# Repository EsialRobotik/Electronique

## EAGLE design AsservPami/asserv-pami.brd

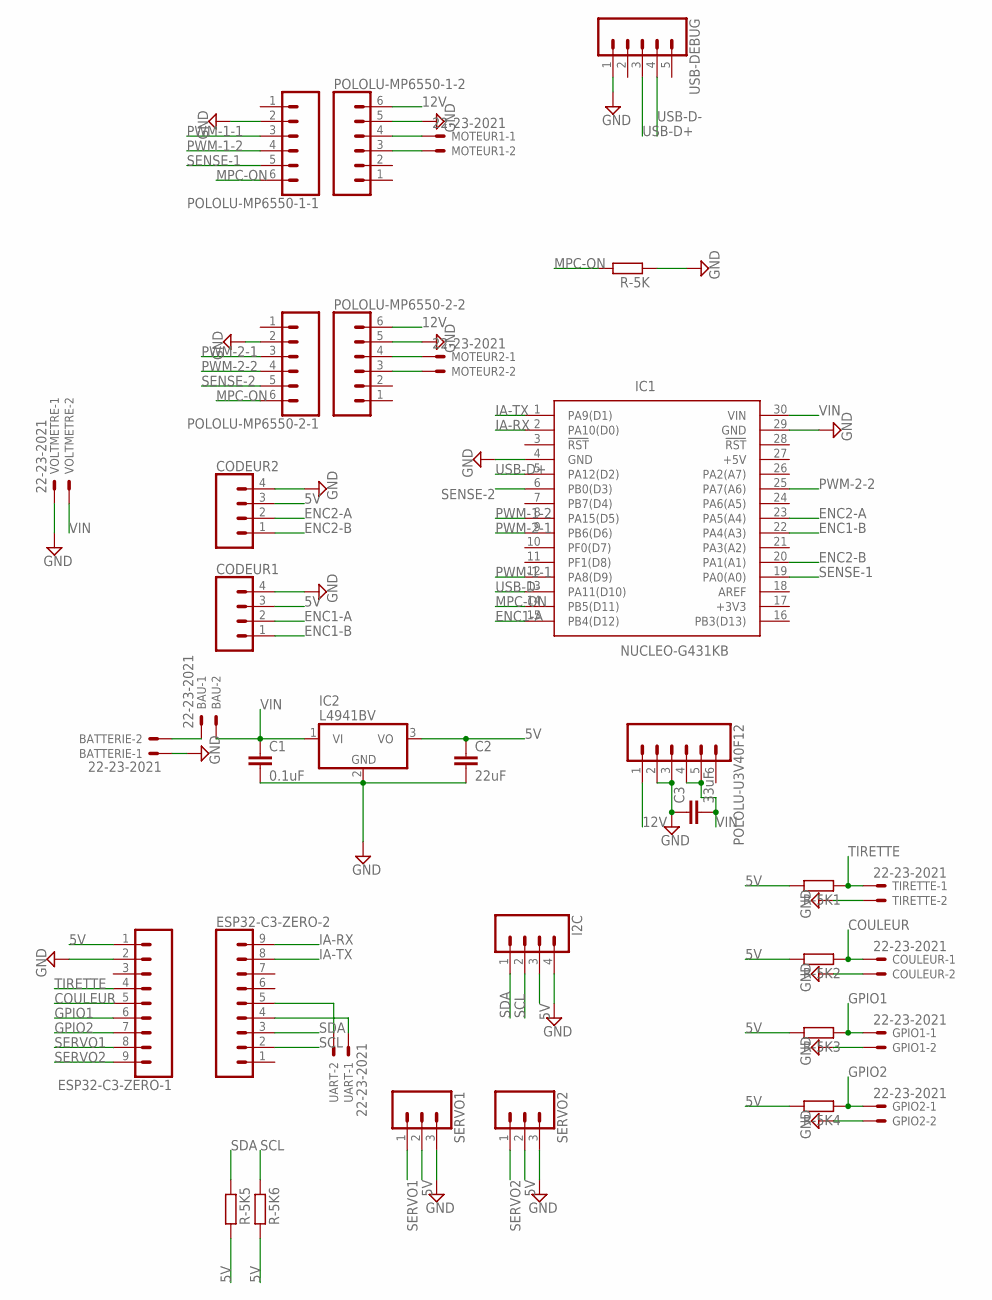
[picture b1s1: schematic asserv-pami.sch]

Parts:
BATTERIE: 22-23-2021
BAU: 22-23-2021
C1: 0.1uF; C5B2.5
C2: 22uF; C5B2.5
C3: 33uF; C5B2.5
CODEUR1, CODEUR2: CONN_04PTH; 1X04
COULEUR: 22-23-2021
ESP32-C3-ZERO-1, ESP32-C3-ZERO-2: CONN_09LONGPADS; 1X09_LONGPADS
GPIO1, GPIO2: 22-23-2021
I2C: CONN_04PTH; 1X04
IC1: NUCLEO-G431KB; DIPS1524W66P254L5029H1500Q30N
IC2: L4941BV; TO220V
MOTEUR1, MOTEUR2: 22-23-2021
POLOLU-MP6550-1-1, POLOLU-MP6550-1-2, POLOLU-MP6550-2-1, POLOLU-MP6550-2-2: CONN_06NO_SILK_FEMALE_PTH; 1X06_NO_SILK
POLOLU-U3V40F12: CONN_06NO_SILK_FEMALE_PTH; 1X06_NO_SILK
R-5K, R-5K1, R-5K2, R-5K3, R-5K4, R-5K5, R-5K6: R-EU_0204/7; 0204/7
SERVO1, SERVO2: CONN_03LONGPADS; 1X03_LONGPADS
TIRETTE: 22-23-2021
UART: 22-23-2021
USB-DEBUG: CONN_05NO_SILK; 1X05_NO_SILK
VOLTMETRE: 22-23-2021

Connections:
5V: C2.1, CODEUR1.3, CODEUR2.3, ESP32-C3-ZERO-1.1, I2C.3, IC2.3 (VO), R-5K1.2, R-5K2.2, R-5K3.2, R-5K4.2, R-5K5.2, R-5K6.2, SERVO1.2, SERVO2.2
12V: POLOLU-MP6550-1-2.6, POLOLU-MP6550-2-2.6, POLOLU-U3V40F12.1
COULEUR: COULEUR.1, ESP32-C3-ZERO-1.5, R-5K2.1
ENC1-A: CODEUR1.2, IC1.15 (PB4(D12))
ENC1-B: CODEUR1.1, IC1.22 (PA4(A3))
ENC2-A: CODEUR2.2, IC1.23 (PA5(A4))
ENC2-B: CODEUR2.1, IC1.20 (PA1(A1))
GND: BATTERIE.1, C1.2, C2.2, C3.1, CODEUR1.4, CODEUR2.4, COULEUR.2, ESP32-C3-ZERO-1.2, GPIO1.2, GPIO2.2, I2C.4, IC1.4 (GND), IC1.29 (GND), IC2.2 (GND), POLOLU-MP6550-1-1.2, POLOLU-MP6550-1-2.5, POLOLU-MP6550-2-1.2, POLOLU-MP6550-2-2.5, POLOLU-U3V40F12.2, POLOLU-U3V40F12.3, R-5K.1, SERVO1.3, SERVO2.3, TIRETTE.2, USB-DEBUG.1, VOLTMETRE.1
GPIO1: ESP32-C3-ZERO-1.6, GPIO1.1, R-5K3.1
GPIO2: ESP32-C3-ZERO-1.7, GPIO2.1, R-5K4.1
IA-RX: ESP32-C3-ZERO-2.9, IC1.2 (PA10(D0))
IA-TX: ESP32-C3-ZERO-2.8, IC1.1 (PA9(D1))
MPC-ON: IC1.14 (PB5(D11)), POLOLU-MP6550-1-1.6, POLOLU-MP6550-2-1.6, R-5K.2
unnamed: MOTEUR1.1, POLOLU-MP6550-1-2.4
unnamed: MOTEUR1.2, POLOLU-MP6550-1-2.3
unnamed: MOTEUR2.1, POLOLU-MP6550-2-2.4
unnamed: MOTEUR2.2, POLOLU-MP6550-2-2.3
unnamed: ESP32-C3-ZERO-2.4, UART.1
unnamed: ESP32-C3-ZERO-2.5, UART.2
unnamed: BATTERIE.2, BAU.1
PWM-1-1: IC1.12 (PA8(D9)), POLOLU-MP6550-1-1.3
PWM-1-2: IC1.8 (PA15(D5)), POLOLU-MP6550-1-1.4
PWM-2-1: IC1.9 (PB6(D6)), POLOLU-MP6550-2-1.3
PWM-2-2: IC1.25 (PA7(A6)), POLOLU-MP6550-2-1.4
SCL: ESP32-C3-ZERO-2.2, I2C.2, R-5K6.1
SDA: ESP32-C3-ZERO-2.3, I2C.1, R-5K5.1
SENSE-1: IC1.19 (PA0(A0)), POLOLU-MP6550-1-1.5
SENSE-2: IC1.6 (PB0(D3)), POLOLU-MP6550-2-1.5
SERVO1: ESP32-C3-ZERO-1.8, SERVO1.1
SERVO2: ESP32-C3-ZERO-1.9, SERVO2.1
TIRETTE: ESP32-C3-ZERO-1.4, R-5K1.1, TIRETTE.1
USB-D+: IC1.5 (PA12(D2)), USB-DEBUG.3
USB-D-: IC1.13 (PA11(D10)), USB-DEBUG.4
VIN: BAU.2, C1.1, C3.2, IC1.30 (VIN), IC2.1 (VI), POLOLU-U3V40F12.4, POLOLU-U3V40F12.5, VOLTMETRE.2

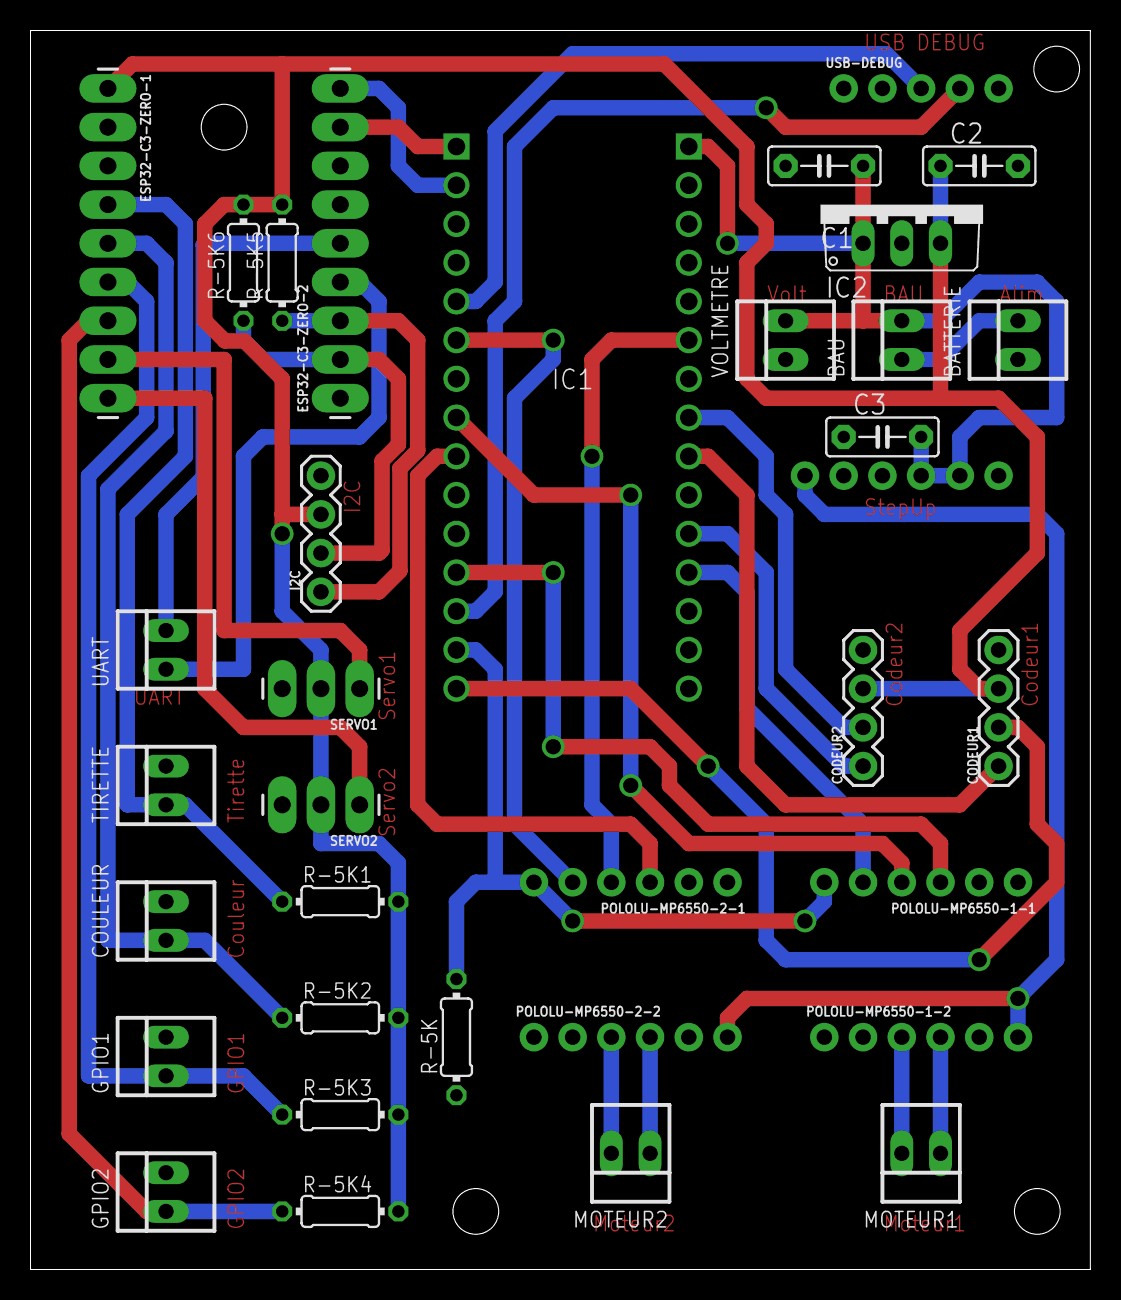
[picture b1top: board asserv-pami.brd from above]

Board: 2 copper layers, 69.5 x 81.3 mm, 35 parts (0 on the bottom side), 34 nets.

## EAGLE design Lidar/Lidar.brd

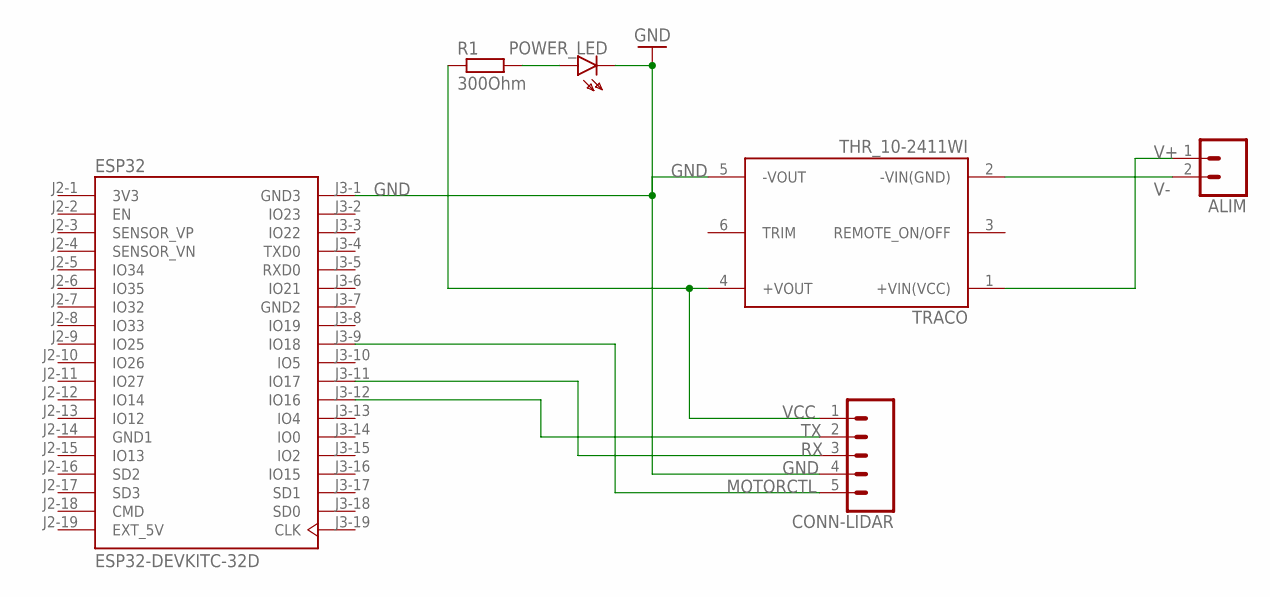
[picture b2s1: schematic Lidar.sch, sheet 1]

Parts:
ALIM: CONN_02POLAR; MOLEX-1X2
CONN-LIDAR: CONN_05PTH; 1X05
ESP32: ESP32-DEVKITC-32D; MODULE_ESP32-DEVKITC-32D
POWER_LED: HLMP6
R1: 300Ohm; 0411/15
TRACO: THR_10-2411WI; CONV_THR_10-2411WI

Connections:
3V3: ESP32.J2-1 (3V3)
GND: CONN-LIDAR.4, ESP32.J3-1 (GND3), POWER_LED.K, TRACO.5 (-VOUT)
GND1: ESP32.J2-14 (GND1)
GND2: ESP32.J3-7 (GND2)
MOTORCTL: CONN-LIDAR.5, ESP32.J3-9 (IO18)
unnamed: POWER_LED.A, R1.2
RX: CONN-LIDAR.3, ESP32.J3-11 (IO17)
TX: CONN-LIDAR.2, ESP32.J3-12 (IO16)
V+: ALIM.1, TRACO.1 (+VIN(VCC))
V-: ALIM.2, TRACO.2 (-VIN(GND))
VCC: CONN-LIDAR.1, ESP32.J2-19 (EXT_5V), R1.1, TRACO.4 (+VOUT)

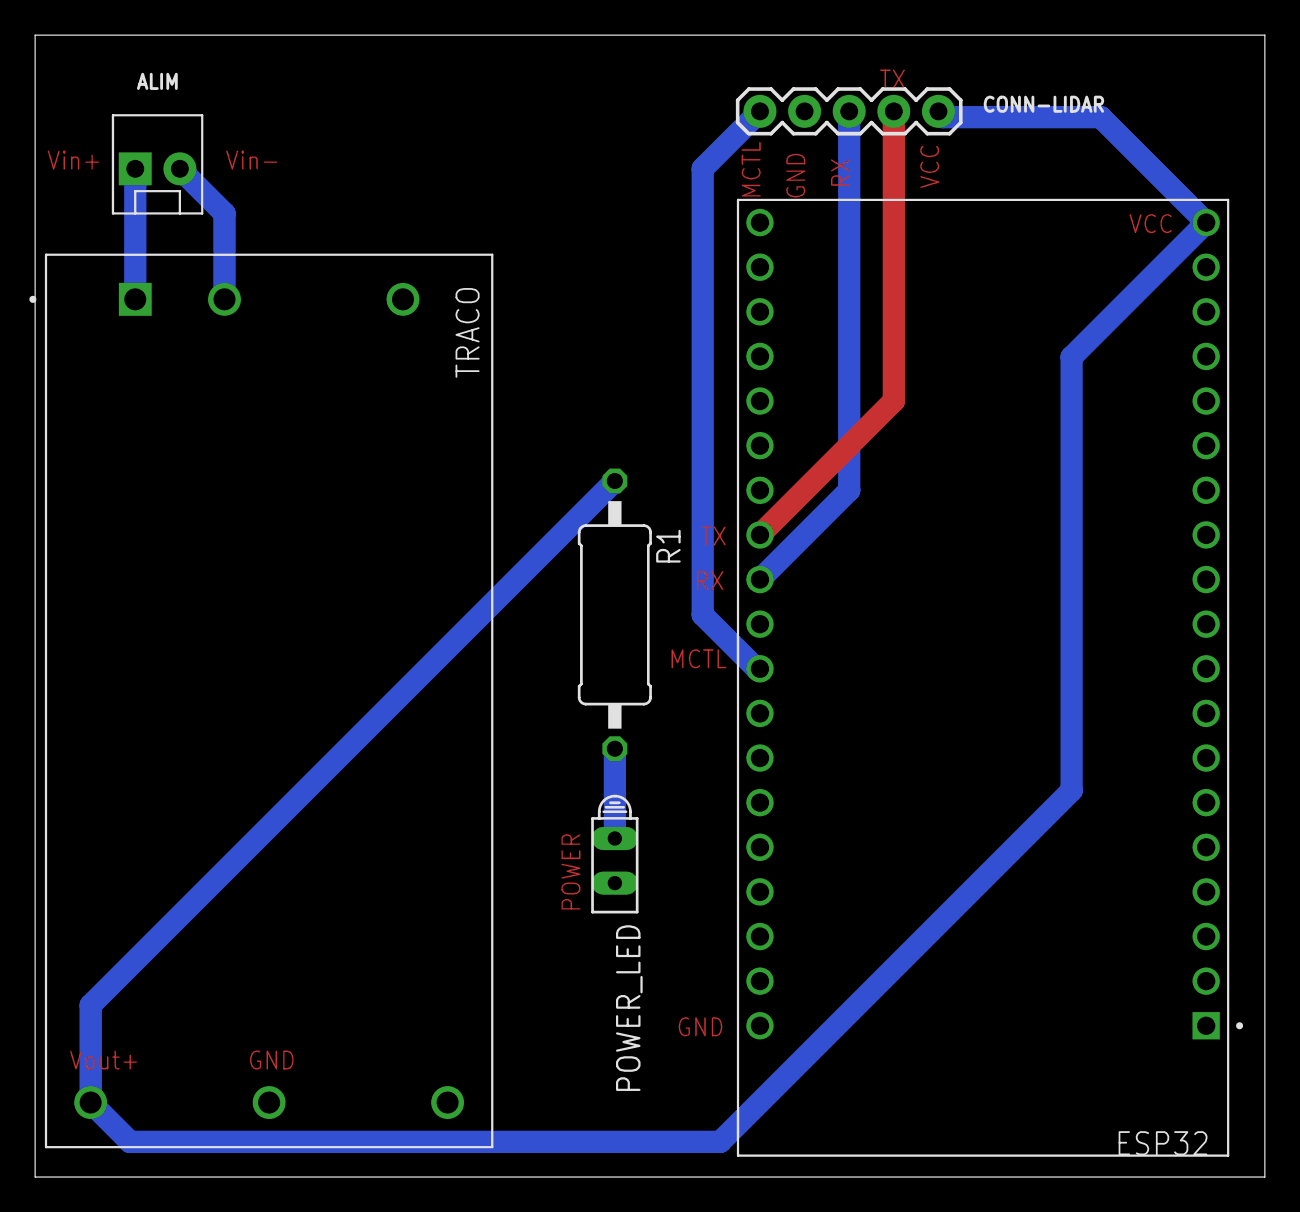
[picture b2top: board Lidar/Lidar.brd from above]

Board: 2 copper layers, 70.0 x 65.0 mm, 6 parts (0 on the bottom side), 8 nets.

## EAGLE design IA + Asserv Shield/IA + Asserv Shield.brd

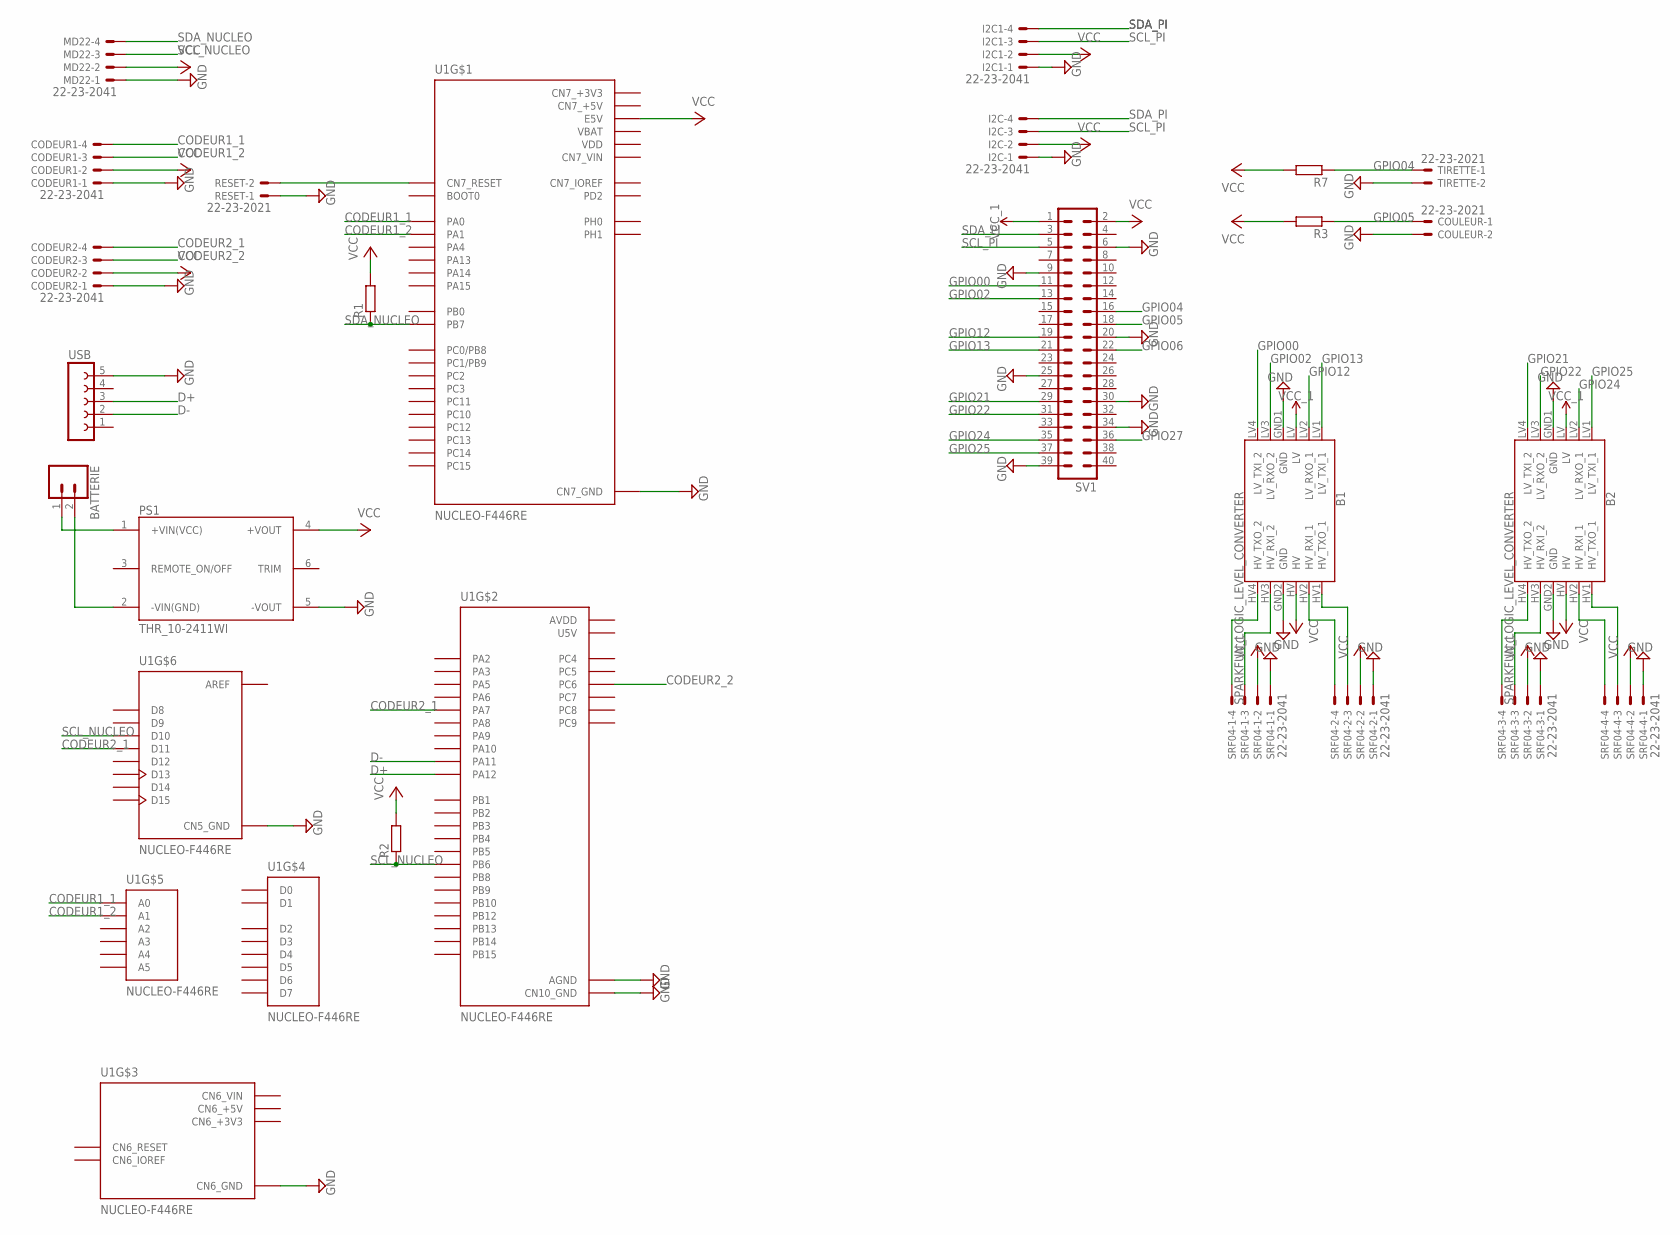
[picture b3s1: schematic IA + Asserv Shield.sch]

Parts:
B1, B2: SPARKFUN_LOGIC_LEVEL_CONVERTER
BATTERIE: CONN_02POLAR; MOLEX-1X2
CODEUR1, CODEUR2: 22-23-2041
COULEUR: 22-23-2021
I2C, I2C1: 22-23-2041
MD22: 22-23-2041
PS1: THR_10-2411WI; CONV_THR_10-2411WI
R1, R2, R3, R7: R-EU_0204/7; 0204/7
RESET: 22-23-2021
SRF04-1, SRF04-2, SRF04-3, SRF04-4: 22-23-2041
SV1: MA20-2
TIRETTE: 22-23-2021
U1: NUCLEO-F446RE; MODULE_NUCLEO-F446RE; MPN NUCLEO-F446RE
USB: FE05-1

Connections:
AREF: U1.CN5_8 (AREF)
AVDD: U1.CN10_7 (AVDD)
CN6_+3V3: U1.CN6_4 (CN6_+3V3)
CN6_+5V: U1.CN6_5 (CN6_+5V)
CN6_VIN: U1.CN6_8 (CN6_VIN)
CN7_+3V3: U1.CN7_16 (CN7_+3V3)
CN7_+5V: U1.CN7_18 (CN7_+5V)
CN7_VIN: U1.CN7_24 (CN7_VIN)
CODEUR1_1: CODEUR1.4, U1.CN7_28 (PA0), U1.CN8_1 (A0)
CODEUR1_2: CODEUR1.3, U1.CN7_30 (PA1), U1.CN8_2 (A1)
CODEUR2_1: CODEUR2.4, U1.CN5_4 (D11), U1.CN10_15 (PA7)
CODEUR2_2: CODEUR2.3, U1.CN10_4 (PC6)
D+: U1.CN10_12 (PA12), USB.3
D-: U1.CN10_14 (PA11), USB.2
GND: B1.GND1 (GND), B1.GND2 (GND), B2.GND1 (GND), B2.GND2 (GND), CODEUR1.1, CODEUR2.1, COULEUR.2, I2C.1, I2C1.1, MD22.1, PS1.5 (-VOUT), RESET.1, SRF04-1.1, SRF04-2.1, SRF04-3.1, SRF04-4.1, SV1.6, SV1.9, SV1.20, SV1.25, SV1.30, SV1.34, SV1.39, TIRETTE.2, U1.CN5_7 (CN5_GND), U1.CN6_6 (CN6_GND), U1.CN6_7 (CN6_GND), U1.CN7_8 (CN7_GND), U1.CN7_19 (CN7_GND), U1.CN7_20 (CN7_GND), U1.CN7_22 (CN7_GND), U1.CN10_9 (CN10_GND), U1.CN10_20 (CN10_GND), U1.CN10_32 (AGND), USB.5
GPIO00: B1.LV4 (LV_TXI_2), SV1.11
GPIO02: B1.LV3 (LV_RXO_2), SV1.13
GPIO04: R7.1, SV1.16, TIRETTE.1
GPIO05: COULEUR.1, R3.1, SV1.18
GPIO06: SV1.22
GPIO12: B1.LV2 (LV_RXO_1), SV1.19
GPIO13: B1.LV1 (LV_TXI_1), SV1.21
GPIO21: B2.LV4 (LV_TXI_2), SV1.29
GPIO22: B2.LV3 (LV_RXO_2), SV1.31
GPIO24: B2.LV2 (LV_RXO_1), SV1.35
GPIO25: B2.LV1 (LV_TXI_1), SV1.37
GPIO27: SV1.36
unnamed: B1.HV2 (HV_RXI_1), SRF04-2.4
unnamed: BATTERIE.1, PS1.1 (+VIN(VCC))
unnamed: BATTERIE.2, PS1.2 (-VIN(GND))
unnamed: RESET.2, U1.CN7_14 (CN7_RESET)
unnamed: B1.HV1 (HV_TXO_1), SRF04-2.3
unnamed: B1.HV3 (HV_RXI_2), SRF04-1.3
unnamed: B1.HV4 (HV_TXO_2), SRF04-1.4
unnamed: B2.HV2 (HV_RXI_1), SRF04-4.4
unnamed: B2.HV1 (HV_TXO_1), SRF04-4.3
unnamed: B2.HV3 (HV_RXI_2), SRF04-3.3
unnamed: B2.HV4 (HV_TXO_2), SRF04-3.4
SCL_NUCLEO: MD22.3, R2.1, U1.CN5_3 (D10), U1.CN10_17 (PB6)
SCL_PI: I2C.3, I2C1.3, SV1.5
SDA_NUCLEO: MD22.4, R1.1, U1.CN7_21 (PB7)
SDA_PI: I2C.4, I2C1.4, SV1.3
U5V: U1.CN10_8 (U5V)
VBAT: U1.CN7_33 (VBAT)
VCC: B1.HV, B2.HV, CODEUR1.2, CODEUR2.2, I2C.2, I2C1.2, MD22.2, PS1.4 (+VOUT), R1.2, R2.2, R3.2, R7.2, SRF04-1.2, SRF04-2.2, SRF04-3.2, SRF04-4.2, SV1.2, U1.CN7_6 (E5V)
VCC_1: B1.LV, B2.LV, SV1.1
VDD: U1.CN7_5 (VDD)

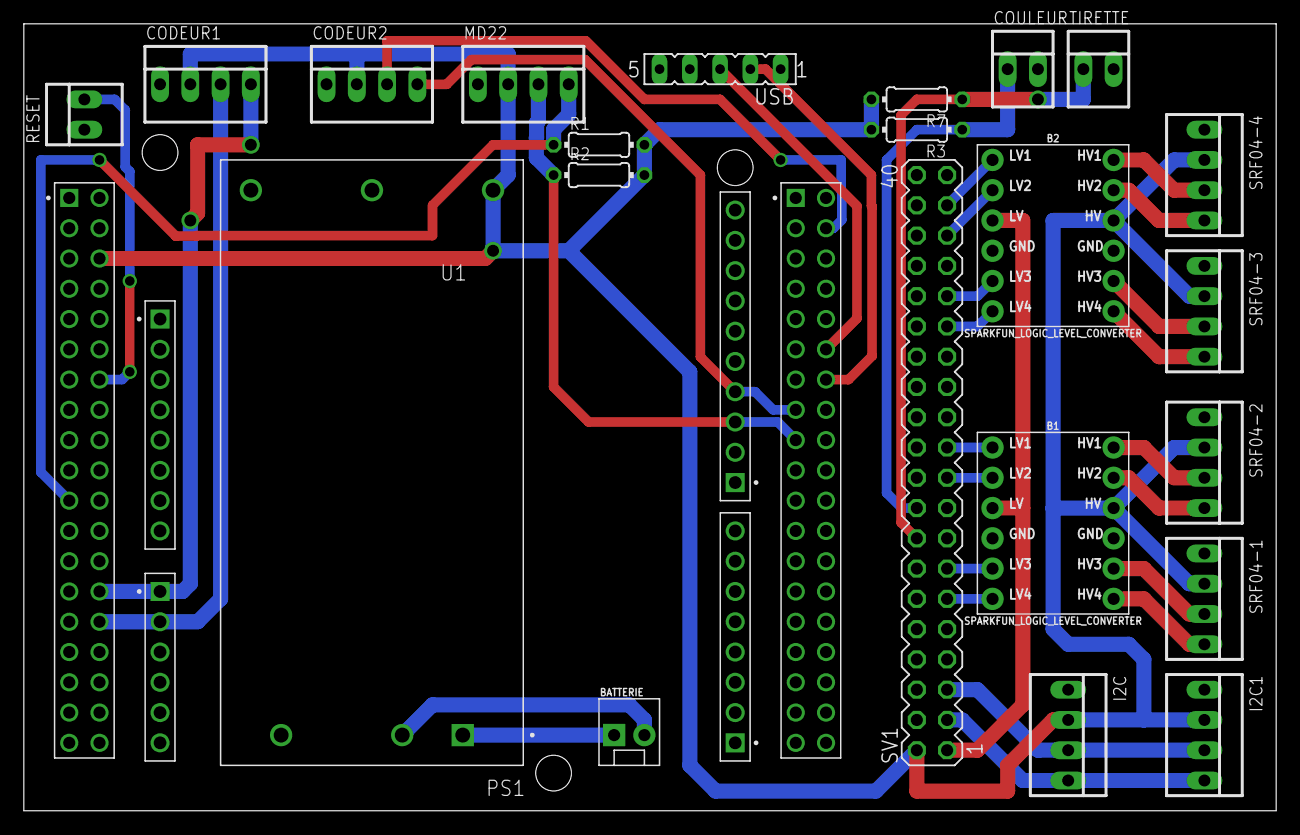
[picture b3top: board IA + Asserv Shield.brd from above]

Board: 2 copper layers, 105.1 x 66.0 mm, 23 parts (0 on the bottom side), 34 nets.

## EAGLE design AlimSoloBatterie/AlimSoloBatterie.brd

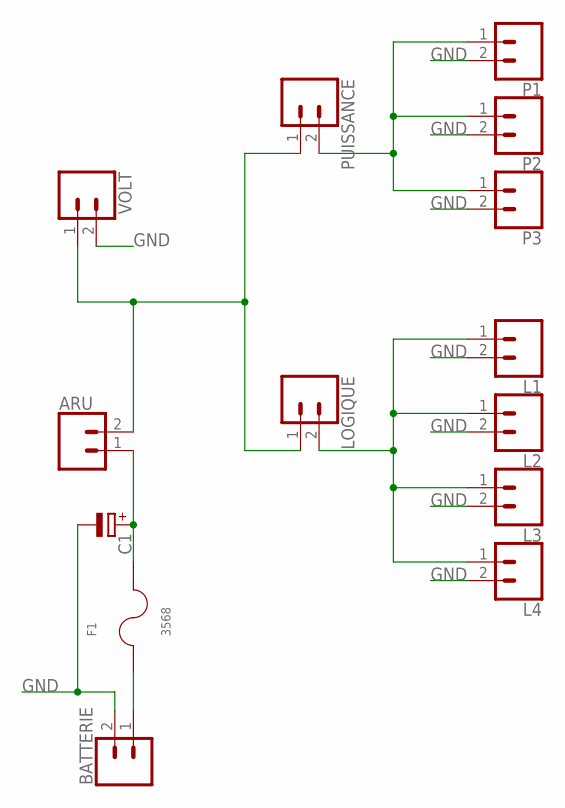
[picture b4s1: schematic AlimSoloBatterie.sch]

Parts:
ARU: CONN_02POLAR; MOLEX-1X2
BATTERIE: CONN_02POLAR; MOLEX-1X2
C1: CPOL-EUE5-13; E5-13
F1: 3568; FUSE_3568
L1, L2, L3, L4: CONN_02POLAR; MOLEX-1X2
LOGIQUE: CONN_02POLAR; MOLEX-1X2
P1, P2, P3: CONN_02POLAR; MOLEX-1X2
PUISSANCE: CONN_02POLAR; MOLEX-1X2
VOLT: CONN_02POLAR; MOLEX-1X2

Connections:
GND: BATTERIE.2, C1.-, L1.2, L2.2, L3.2, L4.2, P1.2, P2.2, P3.2, VOLT.2
unnamed: BATTERIE.1, F1.1, F1.3 (1)
unnamed: ARU.1, C1.+, F1.2, F1.4 (2)
unnamed: ARU.2, LOGIQUE.1, PUISSANCE.1, VOLT.1
unnamed: P1.1, P2.1, P3.1, PUISSANCE.2
unnamed: L1.1, L2.1, L3.1, L4.1, LOGIQUE.2

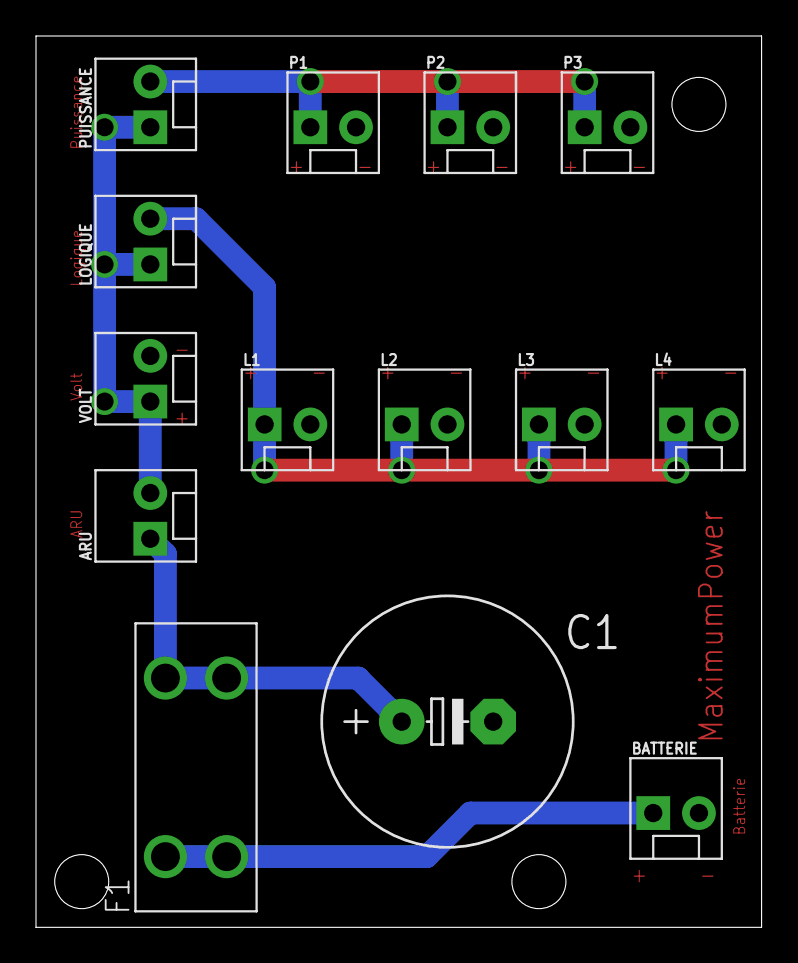
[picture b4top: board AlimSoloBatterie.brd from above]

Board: 2 copper layers, 40.3 x 49.5 mm, 14 parts (0 on the bottom side), 6 nets.

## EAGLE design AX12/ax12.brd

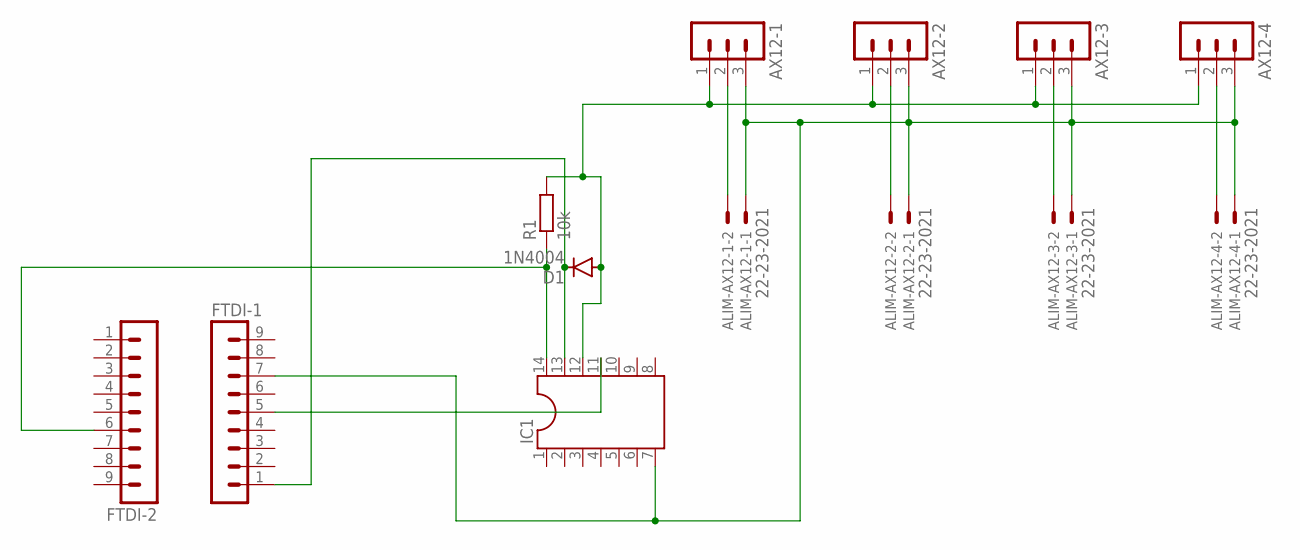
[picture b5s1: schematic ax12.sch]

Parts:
ALIM-AX12-1, ALIM-AX12-2, ALIM-AX12-3, ALIM-AX12-4: 22-23-2021
AX12-1, AX12-2, AX12-3, AX12-4: MA03-1
D1: 1N4004; DO41-10
FTDI-1, FTDI-2: MA09-1
IC1: DIL14
R1: 10k; 0207/12

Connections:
5V: FTDI-2.6, IC1.14, R1.1
AX12-DATA: AX12-1.1, AX12-2.1, AX12-3.1, AX12-4.1, D1.A, IC1.12, R1.2
GND: ALIM-AX12-1.1, ALIM-AX12-2.1, ALIM-AX12-3.1, ALIM-AX12-4.1, AX12-1.3, AX12-2.3, AX12-3.3, AX12-4.3, FTDI-1.7, IC1.7
unnamed: ALIM-AX12-4.2, AX12-4.2
unnamed: ALIM-AX12-3.2, AX12-3.2
unnamed: ALIM-AX12-2.2, AX12-2.2
unnamed: ALIM-AX12-1.2, AX12-1.2
RXD: FTDI-1.5, IC1.11
TXD: D1.C, FTDI-1.1, IC1.13

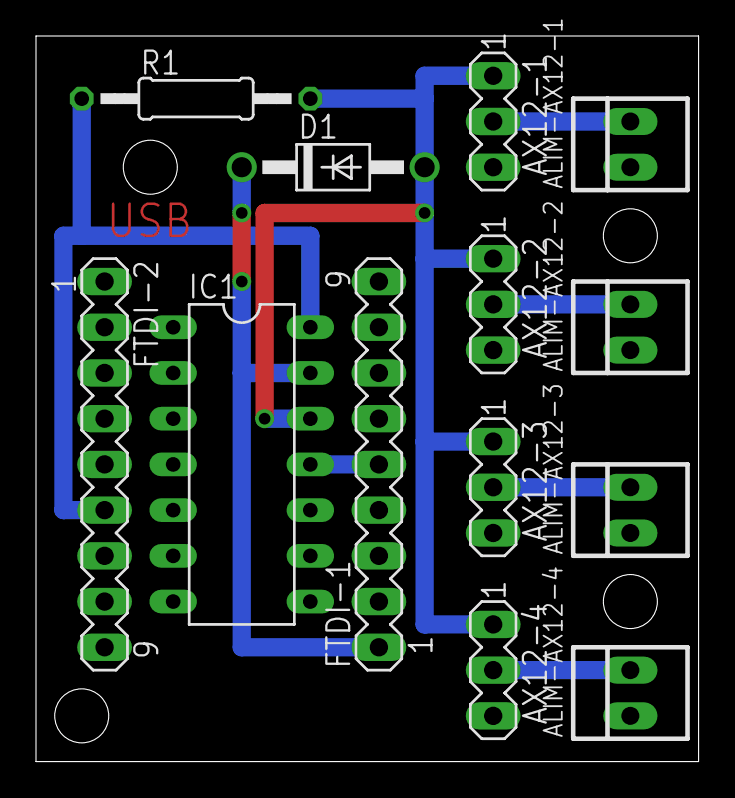
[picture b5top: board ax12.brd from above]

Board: 2 copper layers, 36.8 x 40.3 mm, 13 parts (0 on the bottom side), 9 nets.

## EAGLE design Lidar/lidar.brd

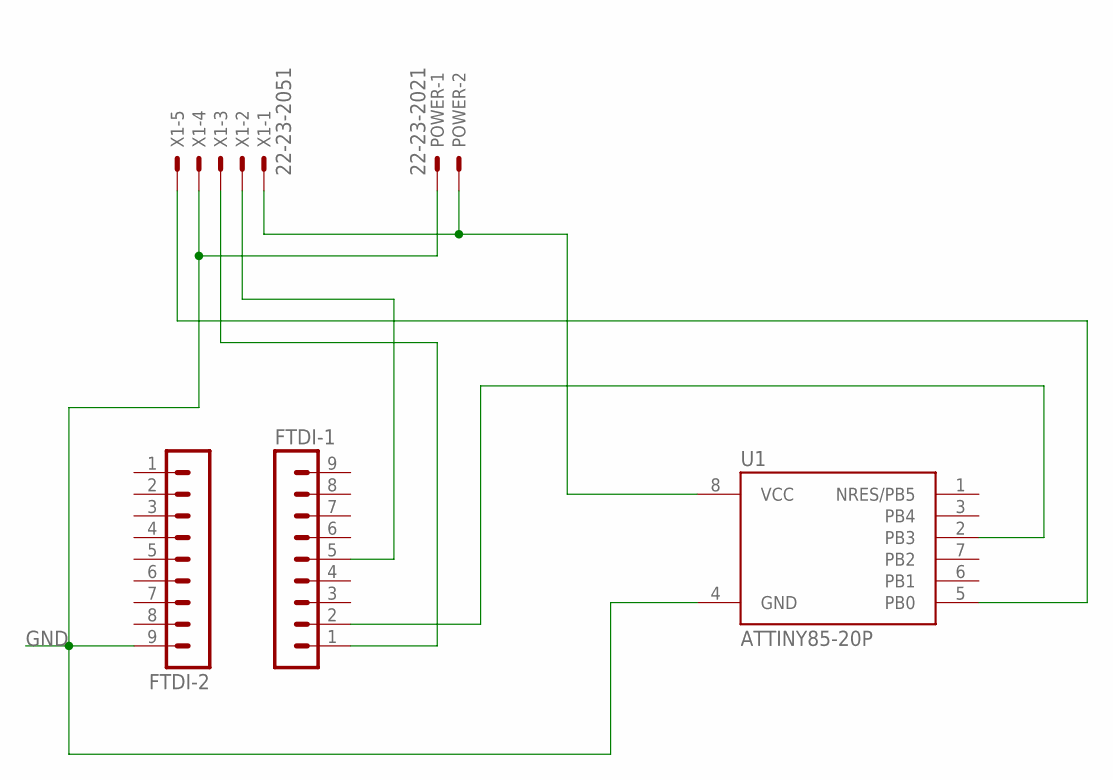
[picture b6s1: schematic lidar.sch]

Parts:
FTDI-1, FTDI-2: MA09-1
POWER: 22-23-2021
U1: ATTINY85-20P; PDIP08_300MIL
X1: 22-23-2051

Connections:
GND: FTDI-2.9, POWER.1, U1.4 (GND), X1.4
unnamed: FTDI-1.2, U1.2 (PB3)
unnamed: POWER.2, U1.8 (VCC), X1.1
unnamed: FTDI-1.5, X1.2
unnamed: FTDI-1.1, X1.3
unnamed: U1.5 (PB0), X1.5

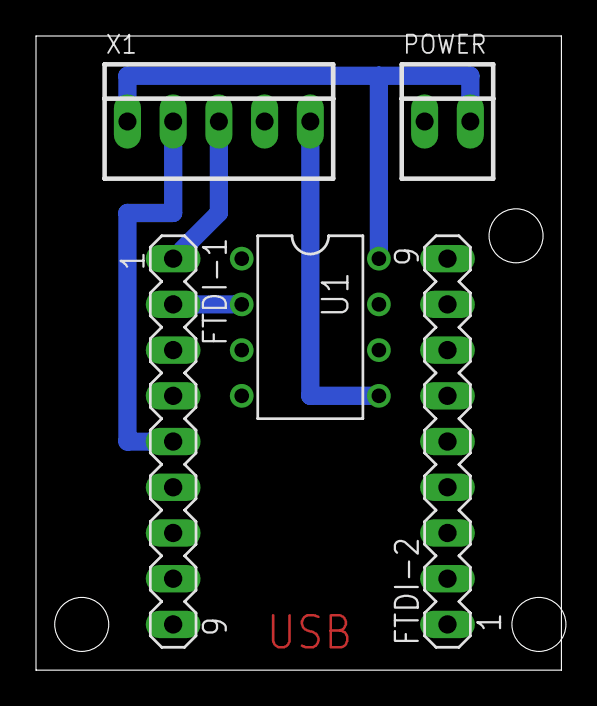
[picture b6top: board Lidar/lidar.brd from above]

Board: 2 copper layers, 29.2 x 35.2 mm, 5 parts (0 on the bottom side), 6 nets.

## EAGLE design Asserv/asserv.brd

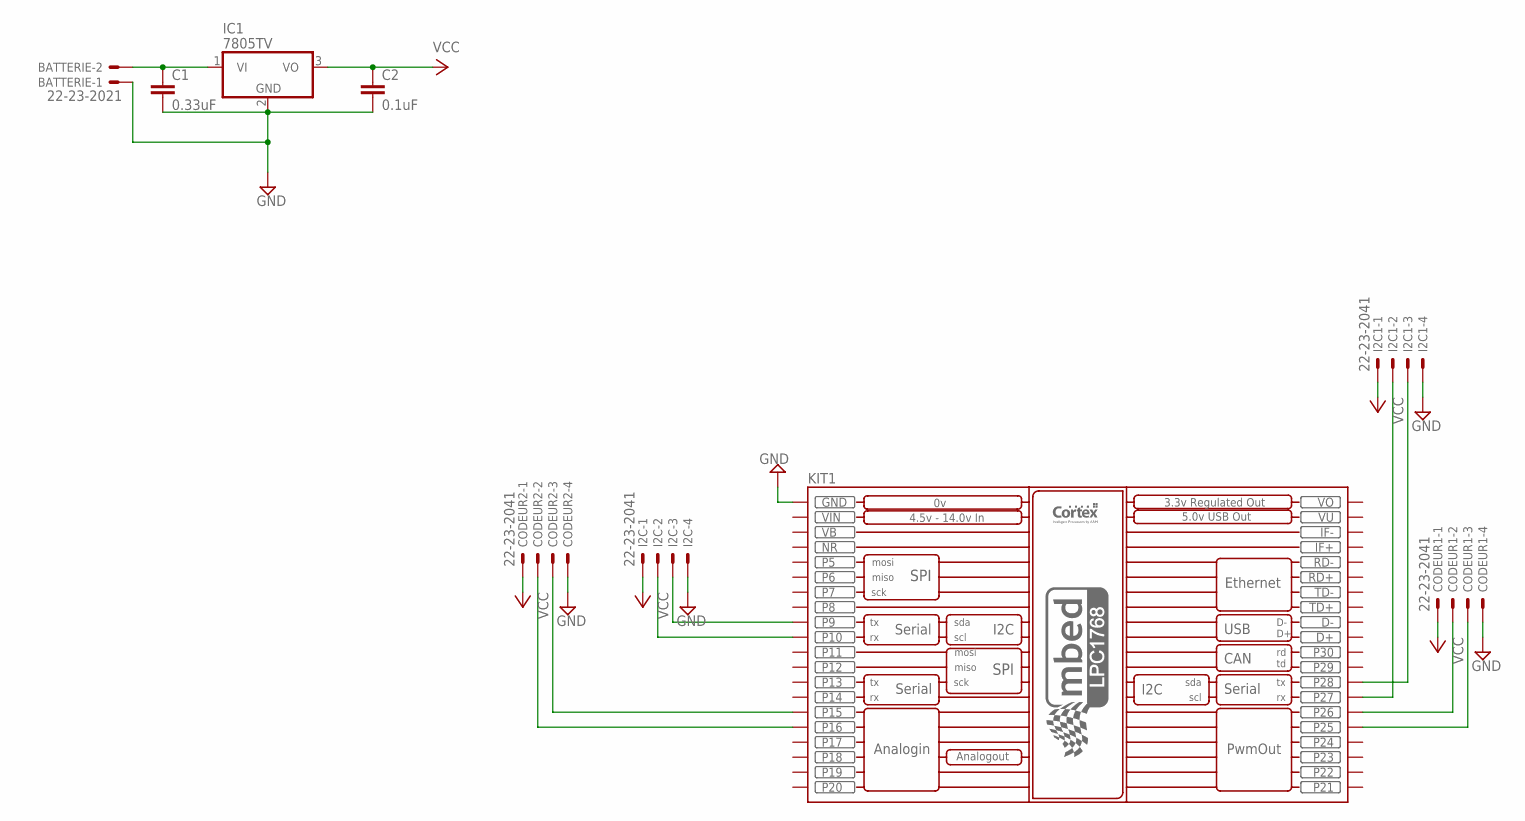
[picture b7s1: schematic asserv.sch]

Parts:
BATTERIE: 22-23-2021
C1: 0.33uF; C5B2.5
C2: 0.1uF; C5B2.5
CODEUR1, CODEUR2: 22-23-2041
I2C, I2C1: 22-23-2041
IC1: 7805TV; TO220V
KIT1: MBED_NXP_LPC1768; MBED-KIT

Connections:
GND: BATTERIE.1, C1.2, C2.2, CODEUR1.4, CODEUR2.4, I2C.4, I2C1.4, IC1.2 (GND), KIT1.GND; also elsewhere on the board
unnamed: BATTERIE.2, C1.1, IC1.1 (VI)
unnamed: I2C1.2, KIT1.P$27 (P27)
unnamed: I2C1.3, KIT1.P$28 (P28)
unnamed 4: KIT1.NR; also elsewhere on the board
unnamed: CODEUR2.3, KIT1.P$15 (P15)
unnamed: CODEUR2.2, KIT1.P$16 (P16)
unnamed: I2C.3, KIT1.P$9 (P9)
unnamed: I2C.2, KIT1.P$10 (P10)
unnamed: CODEUR1.3, KIT1.P$25 (P25)
unnamed: CODEUR1.2, KIT1.P$26 (P26)
VB: KIT1.VB
VCC: C2.1, CODEUR1.1, CODEUR2.1, I2C.1, I2C1.1, IC1.3 (VO)
VIN: KIT1.VIN
VO: KIT1.VOUT (VO)
VU: KIT1.VU

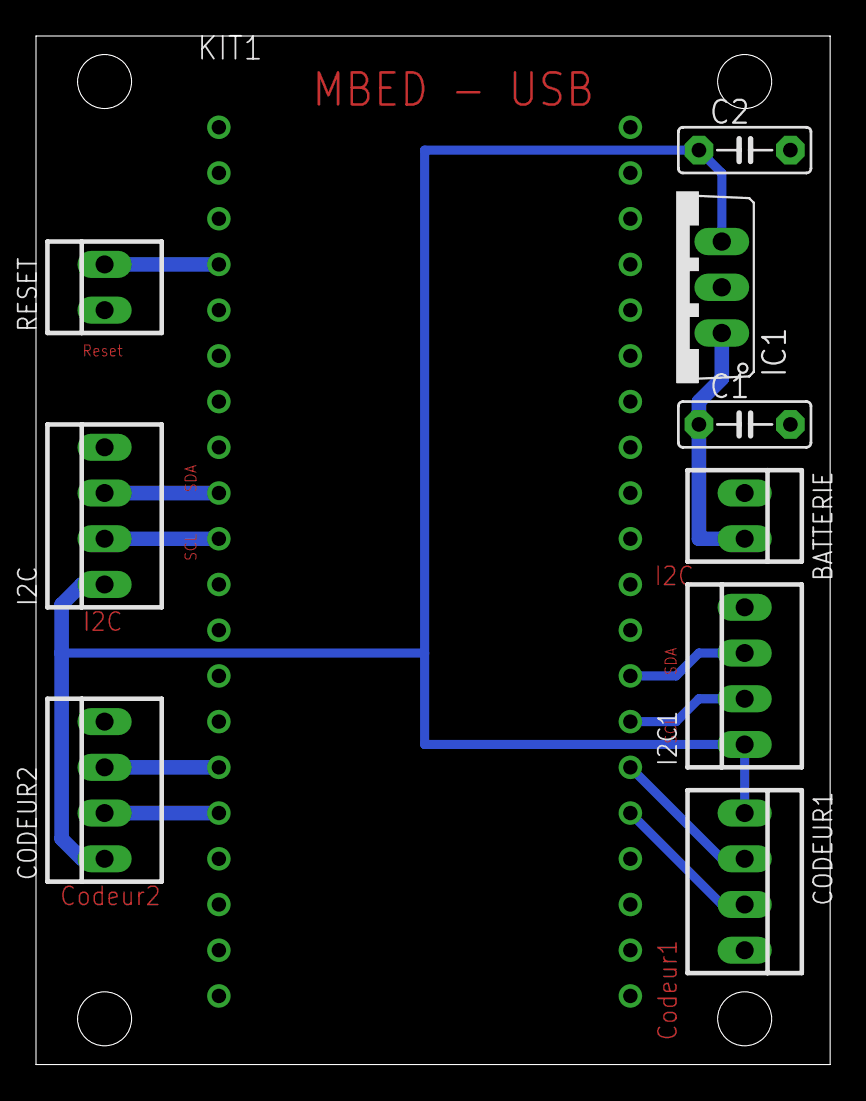
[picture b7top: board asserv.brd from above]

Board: 2 copper layers, 44.1 x 57.1 mm, 10 parts (0 on the bottom side), 12 nets.

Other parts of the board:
RESET: 22-23-2021

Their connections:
GND: RESET.1; also elsewhere on the board
unnamed 4: RESET.2; also elsewhere on the board

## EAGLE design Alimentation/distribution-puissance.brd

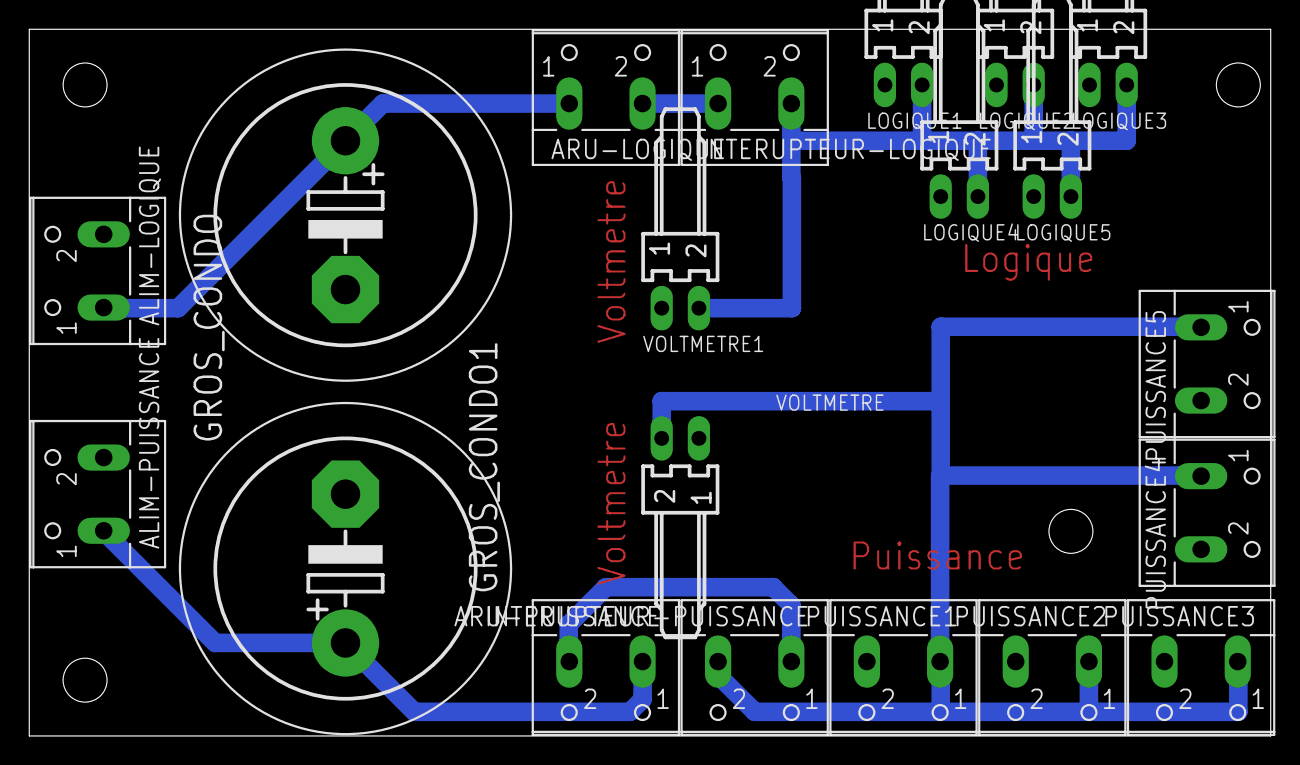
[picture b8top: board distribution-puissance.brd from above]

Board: 2 copper layers, 84.8 x 48.2 mm, 20 parts (0 on the bottom side), 7 nets.

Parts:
ALIM-LOGIQUE: 5V; W237-102
ALIM-PUISSANCE: 19V; W237-102
ARU-LOGIQUE: 5V; W237-102
ARU-PUISSANCE: 19V; W237-102
GROS_CONDO, GROS_CONDO1: EB22,5D
INTERUPTEUR-LOGIQUE: 5V; W237-102
INTERUPTEUR-PUISSANCE: 19V; W237-102
LOGIQUE1, LOGIQUE2, LOGIQUE3, LOGIQUE4, LOGIQUE5: 22-05-7028-02; 7395-02
PUISSANCE1, PUISSANCE2, PUISSANCE3, PUISSANCE4, PUISSANCE5: 19V; W237-102
VOLTMETRE, VOLTMETRE1: 22-05-7028-02; 7395-02

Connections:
GND: ALIM-LOGIQUE.2, ALIM-PUISSANCE.2, GROS_CONDO.-, GROS_CONDO1.-, LOGIQUE1.1, LOGIQUE2.1, LOGIQUE3.1, LOGIQUE4.1, LOGIQUE5.1, PUISSANCE1.2, PUISSANCE2.2, PUISSANCE3.2, PUISSANCE4.2, PUISSANCE5.2, VOLTMETRE.1, VOLTMETRE1.1
unnamed: INTERUPTEUR-PUISSANCE.2, PUISSANCE1.1, PUISSANCE2.1, PUISSANCE3.1, PUISSANCE4.1, PUISSANCE5.1, VOLTMETRE.2
unnamed: INTERUPTEUR-LOGIQUE.2, LOGIQUE1.2, LOGIQUE2.2, LOGIQUE3.2, LOGIQUE4.2, LOGIQUE5.2, VOLTMETRE1.2
unnamed: ALIM-PUISSANCE.1, ARU-PUISSANCE.1, GROS_CONDO.+
unnamed: ALIM-LOGIQUE.1, ARU-LOGIQUE.1, GROS_CONDO1.+
unnamed: ARU-PUISSANCE.2, INTERUPTEUR-PUISSANCE.1
unnamed: ARU-LOGIQUE.2, INTERUPTEUR-LOGIQUE.1

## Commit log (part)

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2017-11-12 carte d'alimentation
2017-11-13 utilisation de bornier pour les ARU + plus grosses pistes dans le routage + gerber files
2018-03-04 carte d'asserv
2018-03-12 carte IA
2018-03-27 ajout d'un i2c sur l'asserv et design de l'ia
2018-04-03 IA: Correction des pullup sur les GPIOs
2018-04-04 routage IA + gerber
2019-03-07 carte puissance v2
2019-03-17 puissance IA + carte AX12
2019-03-25 lidar + reset mbed + trou ax12
2019-03-25 gerber files
2019-04-01 fix board et gerber file
2020-02-16 asserv Nucleo
2020-02-23 maj asserv nucelo
2022-10-09 gerber file for IA V2 + new libraries from mouser + Lidar / Ia / Asserv shield project creation
2023-04-02 Cleaning and new cards
2023-11-18 wip: Lidar schematic
2024-01-13 board schematic
2024-01-14 re-route everything
2024-01-14 (re-)use the VCC pin to avoid 90° routes
2024-01-14 add LIDAR board (power&logic)
    from fusetim-lidar-board:
    * wip: Lidar schematic
    * board schematic
    * re-route everything
    * (re-)use the VCC pin to avoid 90° routes
2024-01-14 add(lidar): POWER LED + reduce the board size
2024-12-19 Asserv PAMI board
2025-02-05 ajout BAU et Voltmetre + label
2025-03-15 for impression
2025-03-15 fix court circuit
2025-03-15 update pdf
2025-03-30 fix i2c
2025-03-30 fix name
2025-05-08 fix pami woard
2025-09-18 carte pami Raspberry
2026-03-21 Correction de iasserv et pamiboard
2026-03-21 schema pdf
2026-03-21 fix alimentation 12V et USB

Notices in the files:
parts and their libraries:
SparkFun-Connectors: Licensing: Creative Commons ShareAlike 4.0 International - https://creativecommons.org/licenses/by-sa/4.0
